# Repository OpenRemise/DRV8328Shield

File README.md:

# DRV8328Shield

<a href="https://openremise.at">
<picture>
  <source media="(prefers-color-scheme: dark)" srcset="https://github.com/OpenRemise/.github/raw/master/data/icons/icon_dark.svg">
  
</picture>
</a>

The DRV8328Shield was a prototype of a shield with [DRV8328](https://www.ti.com/product/DRV8328) in [Arduino](https://www.arduino.cc/) form factor. Due to the inadequacies of the stackable headers, Arduino compatibility was abandoned and single-board solutions are now used.

### Revision A errors
- PVDD should be tied to VIN instead of 5V  
  5V is simply too low to keep the high side switched on continuously

- TPS27S100B doesn't turn off if two consecutive shorts are too close together (see [this](https://e2e.ti.com/support/power-management-group/power-management/f/power-management-forum/1402669/tps27s100-two-consecutive-shorts-second-one-not-recognized) post on the TI forum)  
  This is an issue for the ACK detection. The second ACK would simply get lost in this case.  

  The only reliable fix for this might be to monitor IMON as well. Here is a capture of the second ACK pulse of an MX645 during a DECUP update. IMON is above 500mV for about 8µs.

  As it later turned out this isn't a workaround either.  
  | While some shorts look like this                                                              | Others look like this                                                                       |
  | --------------------------------------------------------------------------------------------- | ------------------------------------------------------------------------------------------- |
  |  |  |

  And that 420mV pulse is too short for a common LM339... now what?

- TPS27S100B could use another 1µF ceramic capacitor at IN (e.g. same as at OUT)

- N and P tracks are reversed  
  We currently generate the signal for INHA (output SHA) with the first half-bit 1 and the second half-bit 0. It must stay that way because we want the RMT end-of-transmission level to be 0. The problem is that a signal with the first half-bit 1 would mark the P and not the N track. Currently we feed SHA into the N pin though.

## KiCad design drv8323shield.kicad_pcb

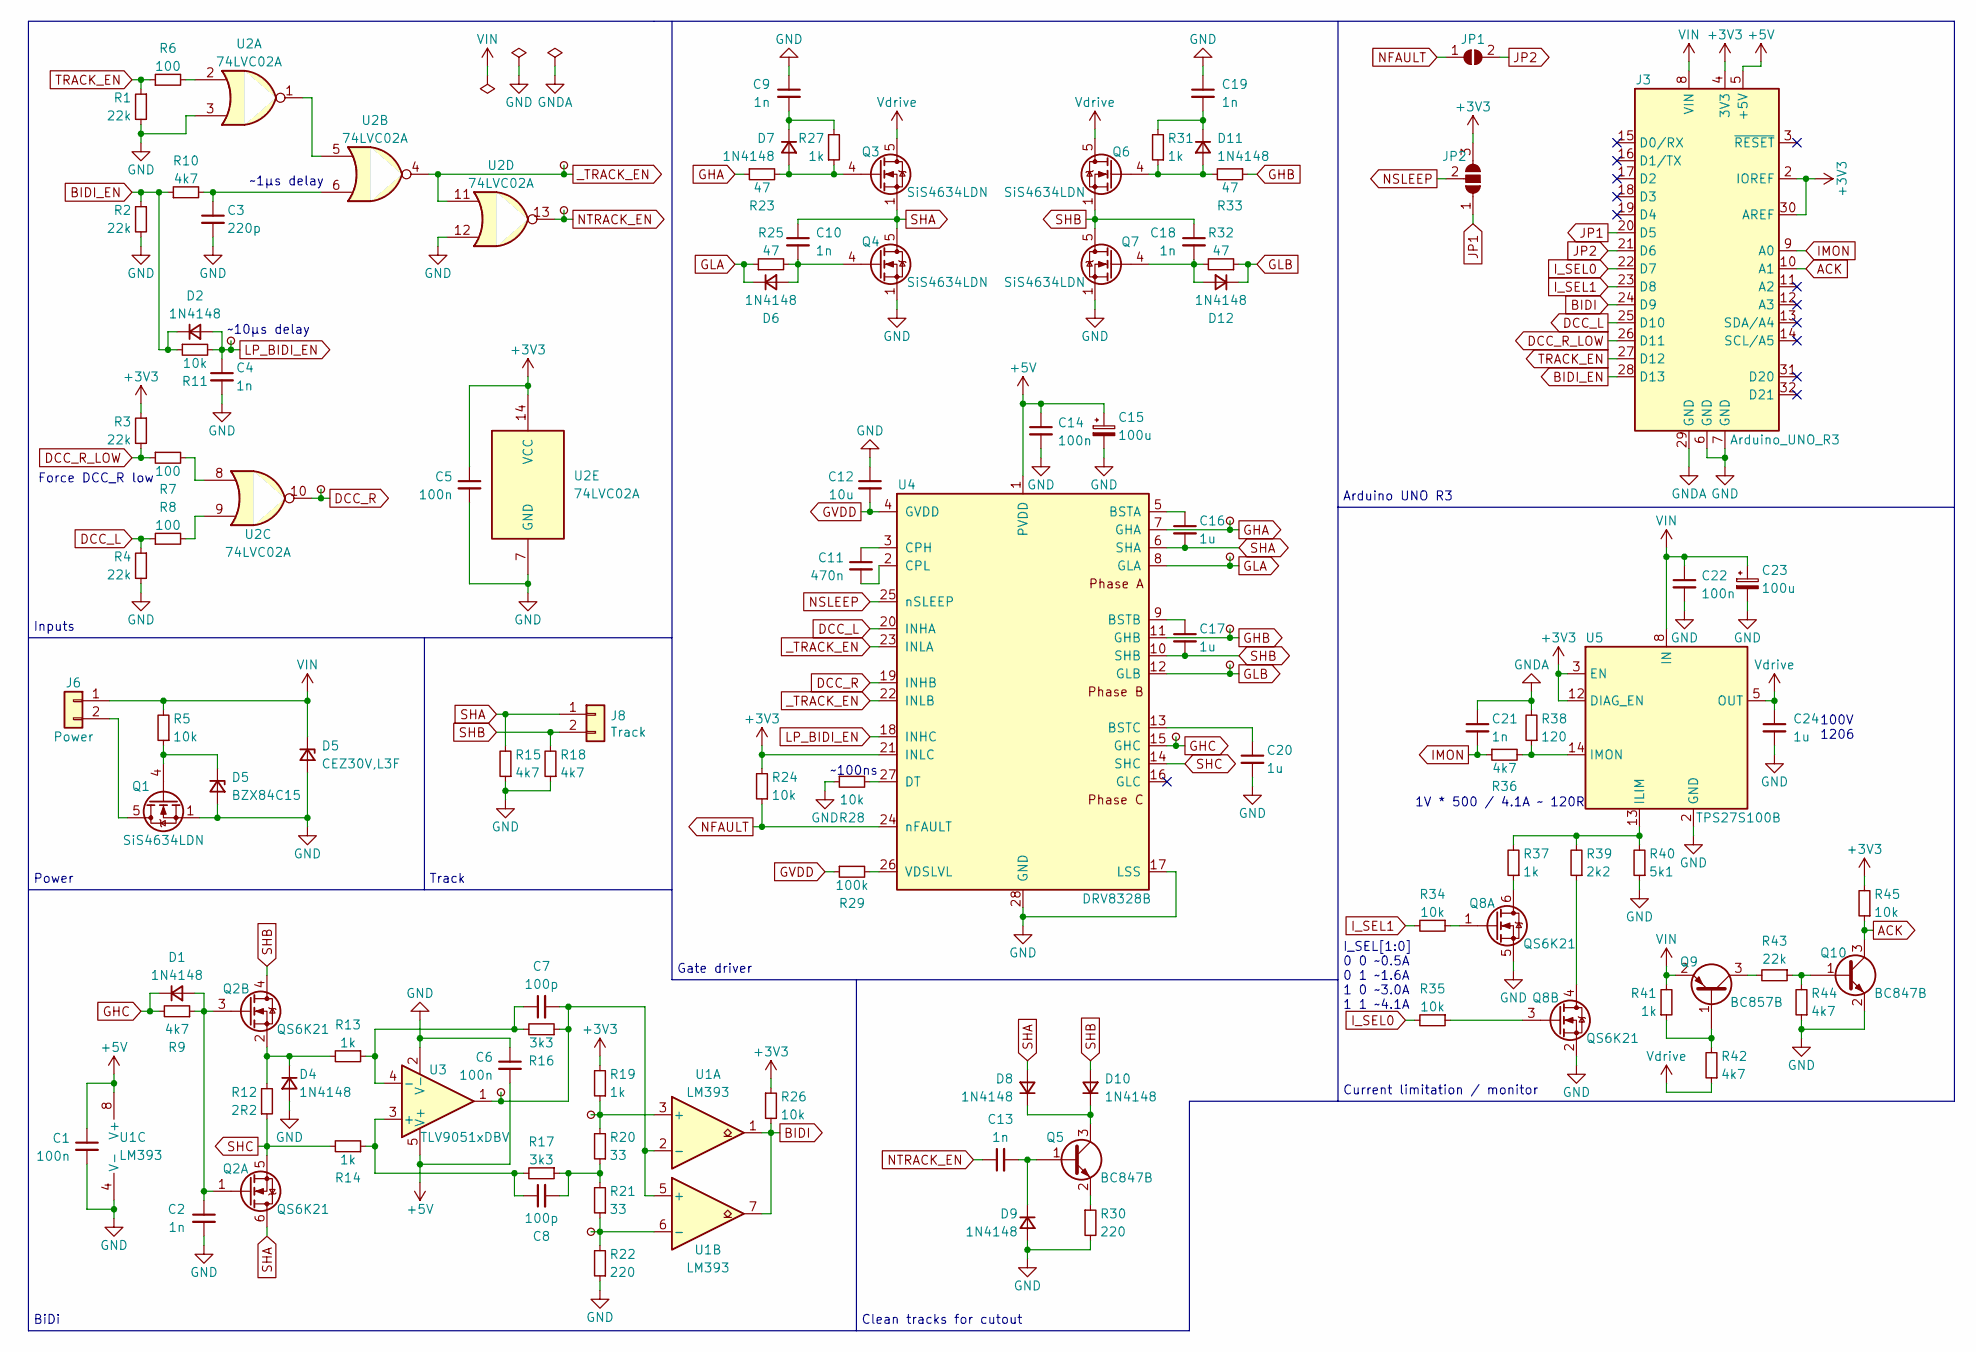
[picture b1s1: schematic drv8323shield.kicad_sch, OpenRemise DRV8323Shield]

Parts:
C1, C5, C6, C14, C22: 100n; C_0402_1005Metric
C2, C4, C9, C10, C13, C18, C19, C21: 1n; C_0402_1005Metric
C3: 220p; C_0402_1005Metric
C7, C8: 100p; C_0402_1005Metric
C11: 470n; C_1206_3216Metric
C12: 10u; C_1206_3216Metric
C15, C23: 100u; CP_Elec_6.3x7.7
C16, C17, C20, C24: 1u; C_1206_3216Metric
D1, D2, D4, D6, D7, D8, D9, D10, D11, D12: 1N4148; D_SOD-523
D5: CEZ30V,L3F; D_SOD-523
J3: Arduino_UNO_R3; Arduino_UNO_R3_WithMountingHoles
J6: Power; PhoenixContact_MC_1,5_2-G-5.08_1x02_P5.08mm_Horizontal
J8: Track; PhoenixContact_MC_1,5_2-G-3.5_1x02_P3.50mm_Horizontal
JP1: SolderJumper_2_Open; SolderJumper-2_P1.3mm_Open_Pad1.0x1.5mm
JP2: SolderJumper_3_Open; SolderJumper-3_P1.3mm_Open_Pad1.0x1.5mm
Q1, Q3, Q4, Q6, Q7: SiS4634LDN; Vishay_PowerPAK_1212-8_Single
Q2, Q8: QS6K21; TSOT-23-6
Q5, Q10: BC847B; SOT-23
Q9: BC857B; SOT-23-3
R1, R2, R3, R4, R43: 22k; R_0402_1005Metric
R5, R11, R24, R26, R28, R34, R35, R45: 10k; R_0402_1005Metric
R6, R7, R8: 100; R_0402_1005Metric
R9, R10, R36, R42, R44: 4k7; R_0402_1005Metric
R12: 2R2; R_0805_2012Metric_Pad1.20x1.40mm_HandSolder
R13, R14, R19, R27, R31, R37, R41: 1k; R_0402_1005Metric
R15, R18: 4k7; R_0805_2012Metric_Pad1.20x1.40mm_HandSolder
R16, R17: 3k3; R_0402_1005Metric
R20, R21: 33; R_0402_1005Metric
R22: 220; R_0402_1005Metric
R23, R25, R32, R33: 47; R_0402_1005Metric
R29: 100k; R_0402_1005Metric
R30: 220; R_0805_2012Metric_Pad1.20x1.40mm_HandSolder
R38: 120; R_0402_1005Metric
R39: 2k2; R_0402_1005Metric
R40: 5k1; R_0402_1005Metric
TP1, TP2, TP3, TP4, TP5, TP6, TP7, TP8, TP9, TP10, TP11, TP12: TestPoint_Small; TestPoint_Pad_1.0x1.0mm
U1: LM393; SOIC-8_3.9x4.9mm_P1.27mm
U2: 74LVC02A; TSSOP-14_4.4x5mm_P0.65mm
U3: TLV9051xDBV; SOT-23-5
U4: DRV8328B; QFN-28-1EP_4x4mm_P0.4mm_EP2.6x2.6mm_ThermalVias
U5: TPS27S100B; HTSSOP-14-1EP_4.4x5mm_P0.65mm_EP3.4x5mm_Mask3x3.1mm_Thermal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

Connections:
+3V3: C5.1, J3.2 (IOREF), J3.4 (3V3), J3.30 (AREF), JP2.3 (B), R3.1, R19.2, R24.2, R26.1, R45.2, U2.14 (VCC), U4.21 (INLC), U5.3 (EN), U5.12 (DIAG_EN)
+5V: C1.1, C6.2, C14.1, C15.1, J3.5 (+5V), U1.8 (V+), U3.5 (V+), U4.1 (PVDD)
ACK: J3.10 (A1), Q10.3 (C), R45.1
BIDI: J3.24 (D9), R26.2, U1.1, U1.7
BIDI_EN: D2.1 (K), J3.28 (D13), R2.1, R10.1, R11.1
DCC_L: J3.25 (D10), R4.1, R8.1, U4.20 (INHA)
DCC_R: TP2.1, U2.10, U4.19 (INHB)
DCC_R_LOW: J3.26 (D11), R3.2, R7.1
GHA: R23.1, TP9.1, U4.7 (GHA)
GHB: R33.1, TP11.1, U4.11 (GHB)
GHC: D1.1 (K), R9.2, TP8.1, U4.15 (GHC)
GLA: D6.1 (K), R25.1, TP10.1, U4.8 (GLA)
GLB: D12.1 (K), R32.1, TP12.1, U4.12 (GLB)
GND: C1.2, C2.2, C3.2, C4.2, C5.2, C6.1, C9.1, C12.1, C14.2, C15.2, C19.1, C20.2, C22.2, C23.2, C24.2, D4.2 (A), D5.2 (A), D9.2 (A), J3.6 (GND), J3.7 (GND), Q1.1 (S), Q1.2 (S), Q1.3 (S), Q4.1 (S), Q4.2 (S), Q4.3 (S), Q7.1 (S), Q7.2 (S), Q7.3 (S), Q8.2 (S), Q8.5 (S), Q10.2 (E), R1.2, R2.2, R4.2, R15.1, R18.1, R22.1, R28.1, R30.2, R40.1, R44.1, U1.4 (V-), U2.3, U2.7 (GND), U2.12, U3.2 (V-), U4.17 (LSS), U4.28 (GND), U4.29 (GND), U5.2 (GND), U5.15 (GND); also elsewhere on the board
GNDA: C21.1, J3.29 (GND), R38.2
GVDD: C12.2, R29.1, U4.4 (GVDD)
IMON: C21.2, J3.9 (A0), R36.1
I_SEL0: J3.22 (D7), R35.2
I_SEL1: J3.23 (D8), R34.2
JP1: J3.20 (D5), JP2.1 (A)
JP2: J3.21 (D6), JP1.2 (B)
LP_BIDI_EN: C4.1, D2.2 (A), R11.2, TP1.1, U4.18 (INHC)
NFAULT: JP1.1 (A), R24.1, U4.24 (nFAULT)
NSLEEP: JP2.2 (C), U4.25 (nSLEEP)
NTRACK_EN: C13.1, TP5.1, U2.13
unnamed: C3.1, R10.2, U2.6
unnamed: C8.2, R17.1, R20.1, R21.2
unnamed: C2.1, D1.2 (A), Q2.1 (G), Q2.3 (G), R9.1
unnamed: D4.1 (K), Q2.2 (S), R12.2, R13.2
unnamed: C10.2, D6.2 (A), Q4.4 (G), R25.2
unnamed: D7.2 (A), Q3.4 (G), R23.2, R27.1
unnamed: C9.2, D7.1 (K), R27.2
unnamed: C13.2, D9.1 (K), Q5.1 (B)
unnamed: D8.1 (K), D10.1 (K), Q5.3 (C)
unnamed: D11.2 (A), Q6.4 (G), R31.1, R33.2
unnamed: C19.2, D11.1 (K), R31.2
unnamed: C18.2, D12.2 (A), Q7.4 (G), R32.2
unnamed 37: Q1.5 (D); also elsewhere on the board
unnamed: Q5.2 (E), R30.1
unnamed: Q8.6 (D), R37.1
unnamed: Q8.1 (G), R34.1
unnamed: Q8.4 (D), R39.1
unnamed: Q8.3 (G), R35.1
unnamed: Q9.1 (B), R41.1, R42.2
unnamed: Q9.3 (C), R43.2
unnamed: Q10.1 (B), R43.1, R44.2
unnamed: R6.2, U2.2
unnamed: R7.2, U2.8
unnamed: R8.2, U2.9
unnamed: R19.1, R20.2, TP6.1, U1.3 (+)
unnamed: C7.2, R16.1, TP3.1, U1.2 (-), U1.5 (+), U3.1
unnamed: R21.1, R22.2, TP7.1, U1.6 (-)
unnamed: U2.1, U2.5
unnamed: C8.1, R14.1, R17.2, U3.3 (+)
unnamed: C7.1, R13.1, R16.2, U3.4 (-)
unnamed: C16.1, U4.5 (BSTA)
unnamed: C17.1, U4.9 (BSTB)
unnamed: C20.1, U4.13 (BSTC)
unnamed: C11.1, U4.3 (CPH)
unnamed: C11.2, U4.2 (CPL)
unnamed: R28.2, U4.27 (DT)
unnamed: R29.2, U4.26 (VDSLVL)
unnamed: R37.2, R39.2, R40.2, U5.13 (ILIM)
unnamed: R36.2, R38.1, U5.14 (IMON)
SHA: C10.1, C16.2, D8.2 (A), Q2.6 (D), Q3.1 (S), Q3.2 (S), Q3.3 (S), Q4.5 (D), R15.2, U4.6 (SHA); also elsewhere on the board
SHB: C17.2, C18.1, D10.2 (A), Q2.4 (D), Q6.1 (S), Q6.2 (S), Q6.3 (S), Q7.5 (D), R18.2, U4.10 (SHB); also elsewhere on the board
SHC: Q2.5 (S), R12.1, R14.2, U4.14 (SHC)
TRACK_EN: J3.27 (D12), R1.1, R6.1
Vdrive: C24.1, Q3.5 (D), Q6.5 (D), R42.1, U5.5 (OUT), U5.6 (OUT), U5.7 (OUT)
_TRACK_EN: TP4.1, U2.4, U2.11, U4.22 (INLB), U4.23 (INLA)

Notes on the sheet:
Track
Inputs
Clean tracks for cutout
~10µs delay
BiDi
1V * 500 / 4.1A ~ 120R
Gate driver
Current limitation / monitor
100V 1206
Power
Force DCC_R low
~100ns
I_SEL[1:0] 0 0 ~0.5A 0 1 ~1.6A 1 0 ~3.0A 1 1 ~4.1A
Arduino UNO R3
~1µs delay

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
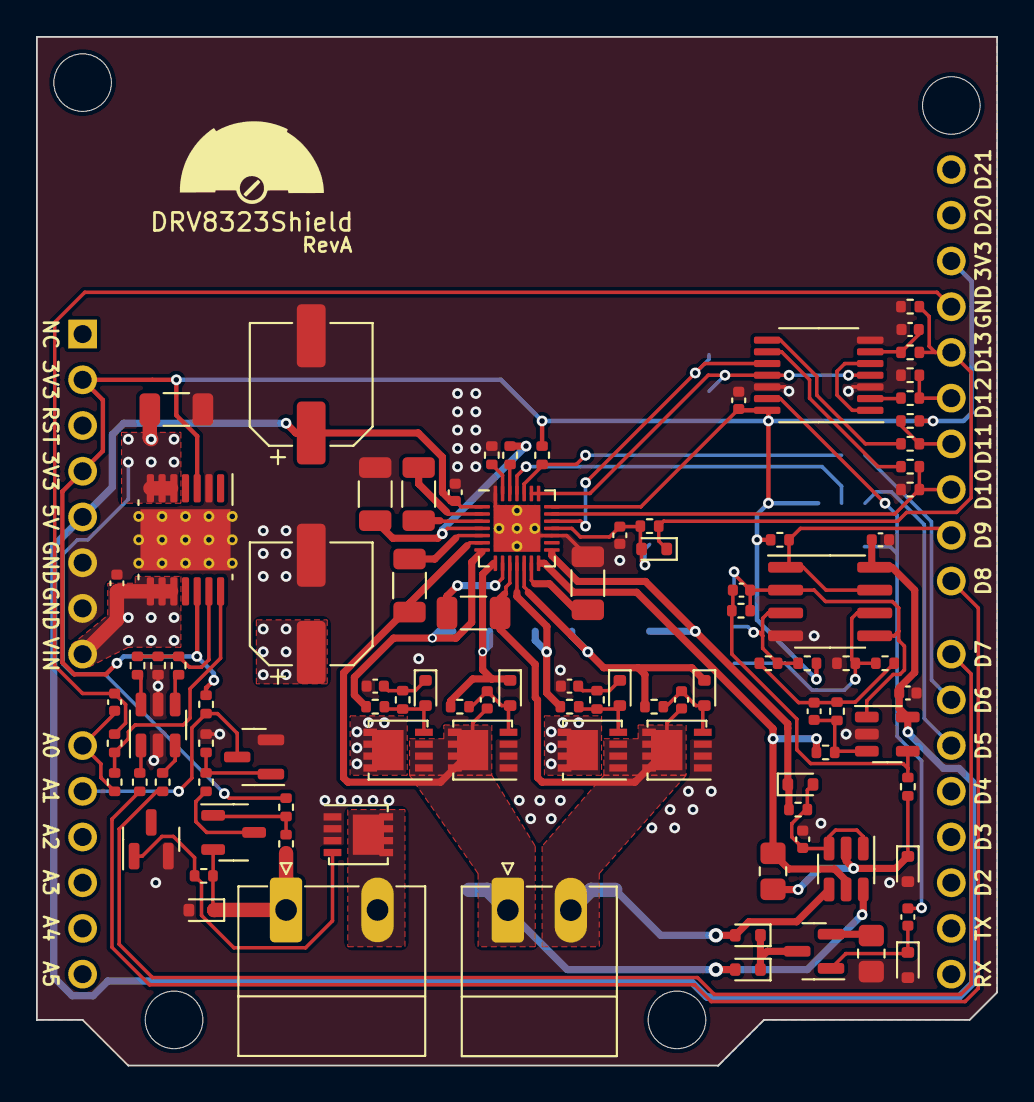
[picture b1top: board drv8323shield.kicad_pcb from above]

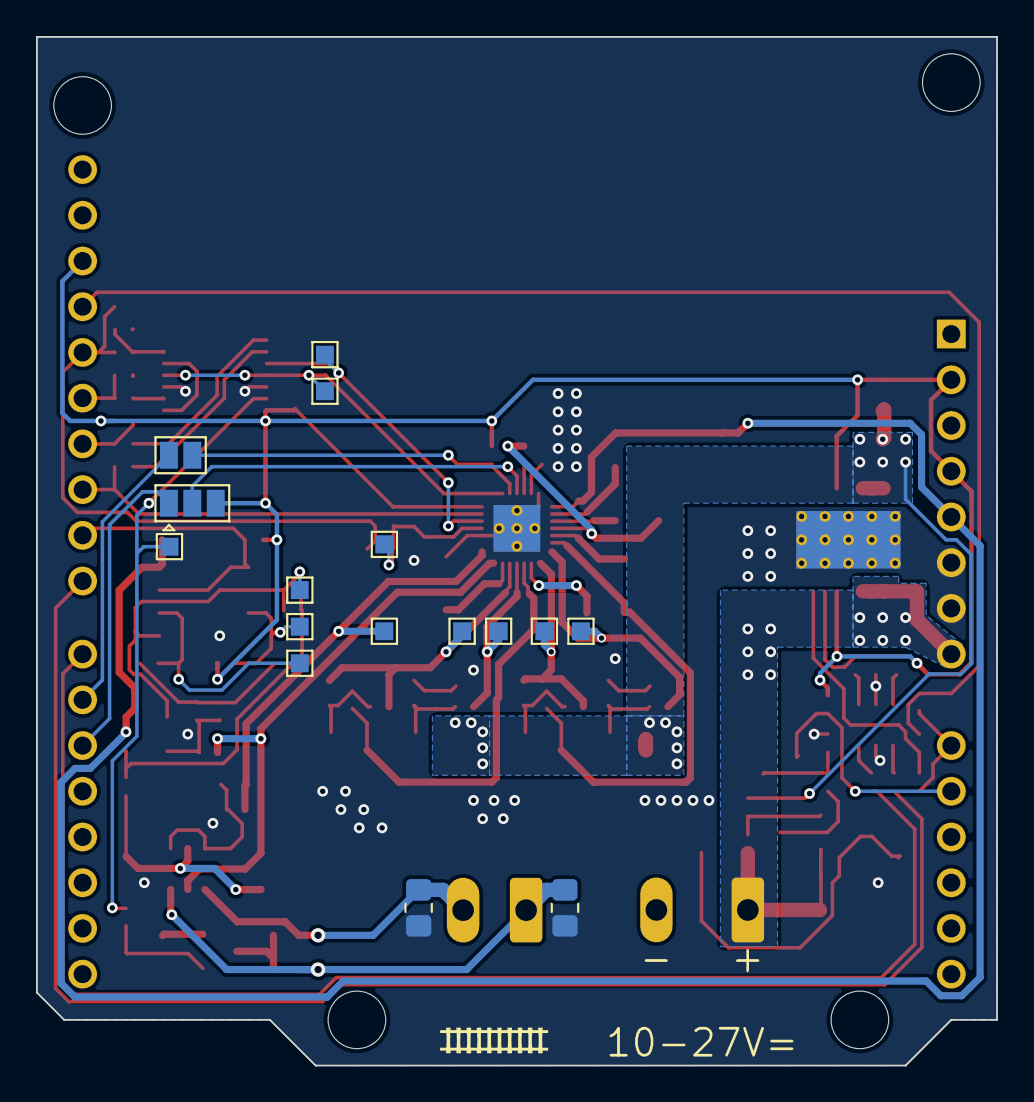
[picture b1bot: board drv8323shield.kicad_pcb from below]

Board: 2 copper layers, 53.3 x 57.2 mm, 113 parts (17 on the bottom side), 72 nets.

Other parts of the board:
D3: BZX84C15; SOT-23
J1: Power; PhoenixContact_MC_1,5_2-G-5.08_1x02_P5.08mm_Horizontal
J2: Track; PhoenixContact_MC_1,5_2-G-3.5_1x02_P3.50mm_Horizontal

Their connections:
GND: D3.2 (A); also elsewhere on the board
unnamed 37: J1.2; also elsewhere on the board
SHA: J2.1; also elsewhere on the board
SHB: J2.2; also elsewhere on the board

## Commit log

2024-01-19 Order RevA
2024-08-16 chore: migrate to KiCad 8.0
2024-08-30 docs: update README with RevA errors
2024-10-24 docs: update README with further findings
2024-11-15 feat: revision A
2024-11-19 feat: archive
